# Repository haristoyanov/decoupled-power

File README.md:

# Linear Decoupled Power Supply

The goal of this project is to create a low-noise, decoupled power supply to power sensitive instrumentation in experimental research laboratories. This power supply will turn 120 VAC wall power into clean, adjustable output DC power, as well as break potential ground loops by being decoupled from the wall power by an isolation barrier. 

This power supply was designed by Mark Carlson at UBC, and we are closely following his original schematics.

# Table of Contents 
- [Motivation](#Motivation)
- [Parts List](#Parts-List)
- [Schematic](#Schematic)
- [Testing](#Testing)
- [Outlook](#Outlook)
- [Acknowledgements](#Acknowledgements)

# Motivation

Low noise, ground-decoupled DC is important for powering ADC/DACs and preamplifiers without introducing noise to the extremely sensitive measurement signals in an experimental condensed matter lab. Currently, the options are a stock DC power supply and a battery power supply. It is possible to improve on the DC power supply in terms of noise level, and the battery (while having low noise) has to be charged and has an unpredictable and possibly dangerous failure mode.
<div align="center">

</div>
</div>
<br/>
<br/>

# Parts List 
Below is a list of all circuit parts used for this project, excluding the Printed Circuit Boards themselves, which were ordered from OSHpark. The PCB design and schematics are included in the PCB folder of this repository. 

<div align="center">

</div>

<br/>
<br/>

# Schematic 

This summary explains the relevant parts of the circuit from left to right.
1. The transformer takes wall power (120V AC at 60Hz) and outputs 16V AC at 60 Hz. This is the input to the power supply.
2. The diodes rectify the current, so that the top branch always has positive voltage and the bottom branch always has negative voltage.
3. The positive and negative voltage regulator ICs (TL1963A and LM2991, respectively) are supplied by the rectified AC, and decoupled using the capacitors to ground (filtering high-frequency noise and preventing output coupling to spikes or dips in the input AC). These output a DC voltage, with a shutdown (SHDN) indicator to show if they are working.
4. The exact output voltage is determined by the voltage on the ADJ pin. The 13K/1K voltage divider sets an output voltage of ±16 V on each branch.
5. The second stage of the circuit is powered by the ±16V. The first component is the 10V voltage reference IC (REF102), which outputs a more precise DC voltage than a voltage regulator. However, it only allows small current draw.
6. To set the exact output voltage, the two op-amp ICs (which are powered from the ±16V DC) take the 10V input from the voltage reference and output a voltage set by the voltage divider consisting of R35 and R36. In the given schematic, this outputs 15V from the top branch and -15V from the bottom.
7. The second op-amp matches and inverts the output of the first, ensuring a linear relationship between the positive and negative output.
8. The two transistors (Q30 and Q31) allow for more current draw from the 16V supply. This current is limited by the voltage regulator ICs, which allow 1A of current to flow.
9. The output goes through an Ethernet-style connector, whose indicator lights indicate whether each branch is outputing a voltage.

<div align="center">

</div>

# Testing

The first testing after confirming a ±15V DC output involved determining the Power Supply Rejection Ratio (PSRR), which describes how well the power supply attenuates noise at a frequency of interest. The PSRR is defined as the 20 times the logarithm of the input to output voltage ripple ratio at 60 Hz. As such, an ideal DC power supply has an infinite PSRR.

<div align="center">

</div>

The testing was conducted through a capacitor to the analog input of a Stanford Research Systems SR1 spectrum analyzer.

Preliminary results indicate a power supply rejection ratio (from 120V AC wall power) of approximately 160. This compares to roughly 100 for the DC power supply that is currently used (Acopian TD15-40, estimated from the voltage ripple quoted in its datasheet). Below is a graph of root-mean-squared Voltage versus frequency on logarithmic axes for a narrow range of frequencies around 60 Hz. We used the data displayed in this plot to calculate our PSRR. 

<div align="center">

</div>

<br />
<br />
It is also of interest to examine the performance of our power supply at a wide range of frequencies. Below is a plot of the voltage noise spectral density (V/rtHz) against the frequency (Hz) on logarithmic axes for a frequency range of 0 Hz to 1500 Hz. To get the total voltage noise in a certain bandwidth, one must integrate the square of the spectral density across that bandwidth and then take the square root of the result. After performing a rough integration across a bandwidth ranging from 10 Hz to 1500 Hz using the method described above, we found that the total voltage noise was reduced by a factor of approximately 100,000.

<div align="center">

</div>

<br />
<br />

More figures and the code used to analyze this data can be found in the appropriately named folders of this repository. 

# Outlook
We will machine protective boxes for convenience. Also, we will try to implement potentiometers to create an adjustable output.

# Acknowledgements
Thank you to the instructors, TAs, and our classmates for UCSB PHYS 13CL/CS15C, thank you to the Dr. Young and all the Young lab grad students and postdocs that helped us, and thank you to Dr. Folk and Mark Carlson at UBC for the schematics and designs.

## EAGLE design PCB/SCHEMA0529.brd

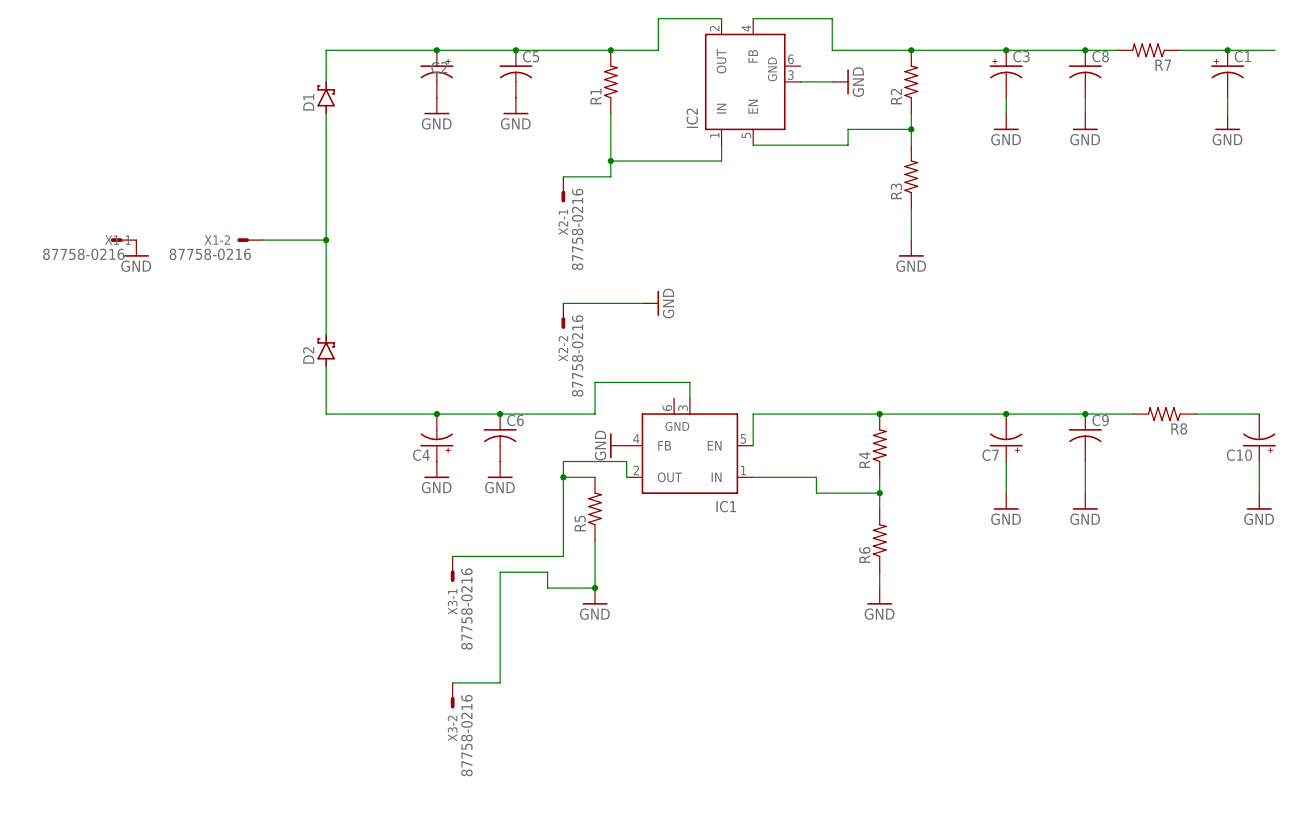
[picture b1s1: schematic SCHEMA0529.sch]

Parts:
C1, C10: CPOL-USTT5D10; TT5D10
C2, C4: CPOL-USE7.5-18; E7,5-18
C3, C7: CPOL-USD/7343-31R; D/7343-31R
C5, C6, C8, C9: C-USC0805; C0805
D1, D2: SCHOTTKY-DIODESMD; SMB
IC1, IC2: LM2596S; TO263-5
R1, R2, R3, R4, R5, R6, R7, R8: R-US_R0805; R0805
X1, X2, X3: 87758-0216

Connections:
GND: C1.-, C2.-, C3.-, C4.+, C5.2, C6.2, C7.+, C8.2, C9.2, C10.+, IC1.4 (FB), IC1.6 (GND), IC2.3 (GND), IC2.6 (GND), R3.1, R5.1, R6.1, X1.1, X2.2, X3.2
unnamed: D1.A, D2.C, X1.2
unnamed: C2.+, C5.1, D1.C, IC2.2 (OUT), R1.2
unnamed: C4.-, C6.1, D2.A, IC1.3 (GND)
unnamed: IC2.1 (IN), R1.1, X2.1
unnamed: C3.+, C8.1, IC2.4 (FB), R2.2, R7.2
unnamed: IC2.5 (EN), R2.1, R3.2
unnamed: C7.-, C9.1, IC1.5 (EN), R4.2, R8.2
unnamed: IC1.1 (IN), R4.1, R6.2
unnamed: IC1.2 (OUT), R5.2, X3.1
unnamed: C1.+, R7.1
unnamed: C10.-, R8.1

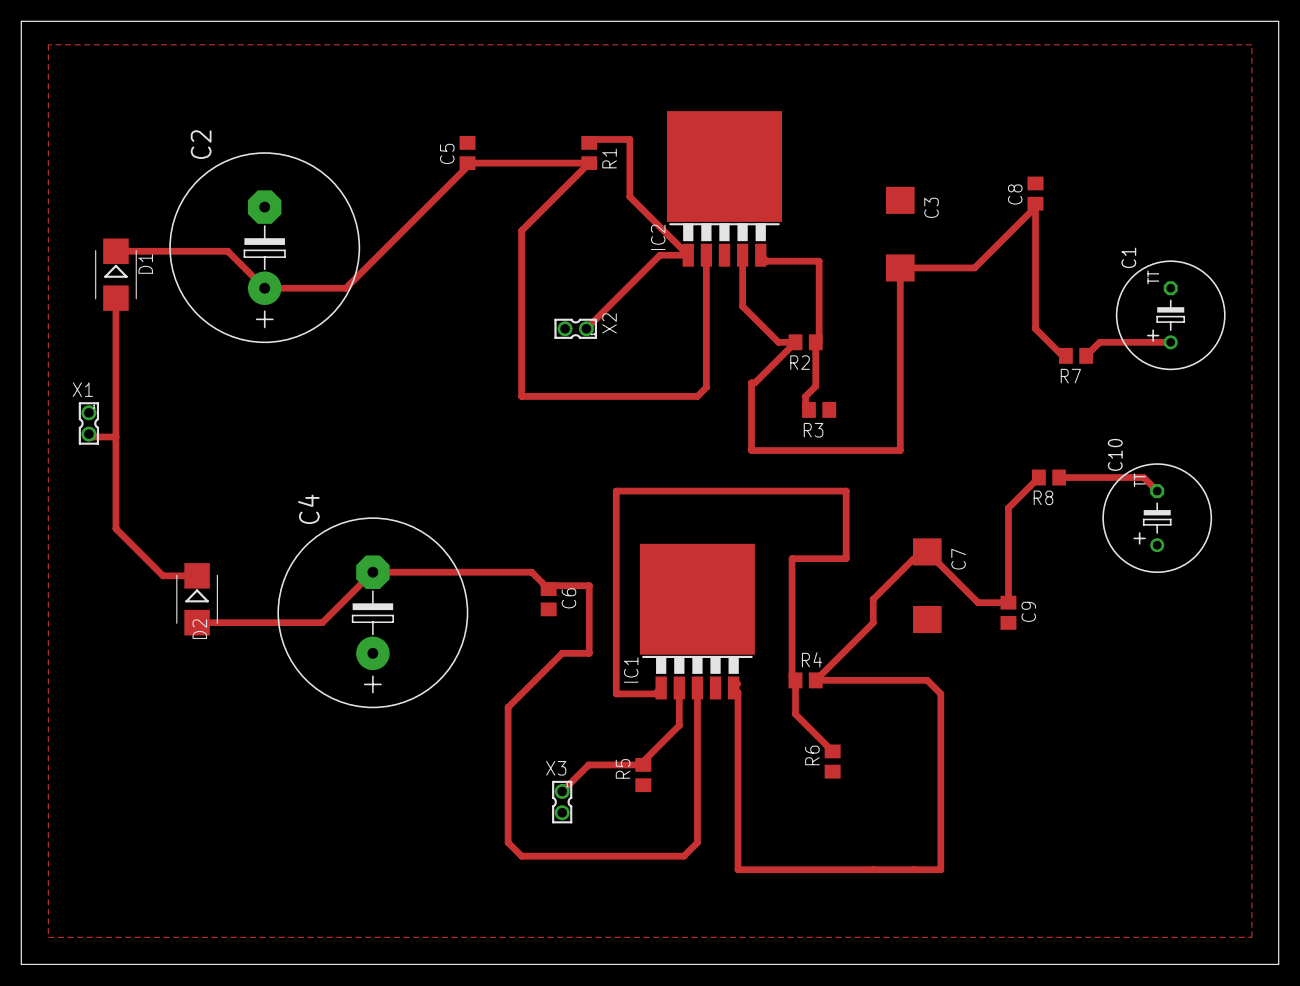
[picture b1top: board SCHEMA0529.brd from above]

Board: 2 copper layers, 118.1 x 88.6 mm, 25 parts (0 on the bottom side), 12 nets.

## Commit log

2023-05-31 Create pcB
2023-06-10 Adding our presentation
2023-06-10 Created desc. and folder for test code
2023-06-10 Create 0README
2023-06-10 Update 0README
2023-06-10 Create temp
2023-06-10 Create RMS Voltage PSSR Calculation
2023-06-10 Create 0Description
2023-06-10 Update 0Description
2023-06-10 Rename 0Description to 00Description
2023-06-10 Rename 00Description to 00FileDescription
2023-06-10 Rename 0Description to 00FileDescription
2023-06-10 Create 00FileDescription
2023-06-10 Create 00Description
